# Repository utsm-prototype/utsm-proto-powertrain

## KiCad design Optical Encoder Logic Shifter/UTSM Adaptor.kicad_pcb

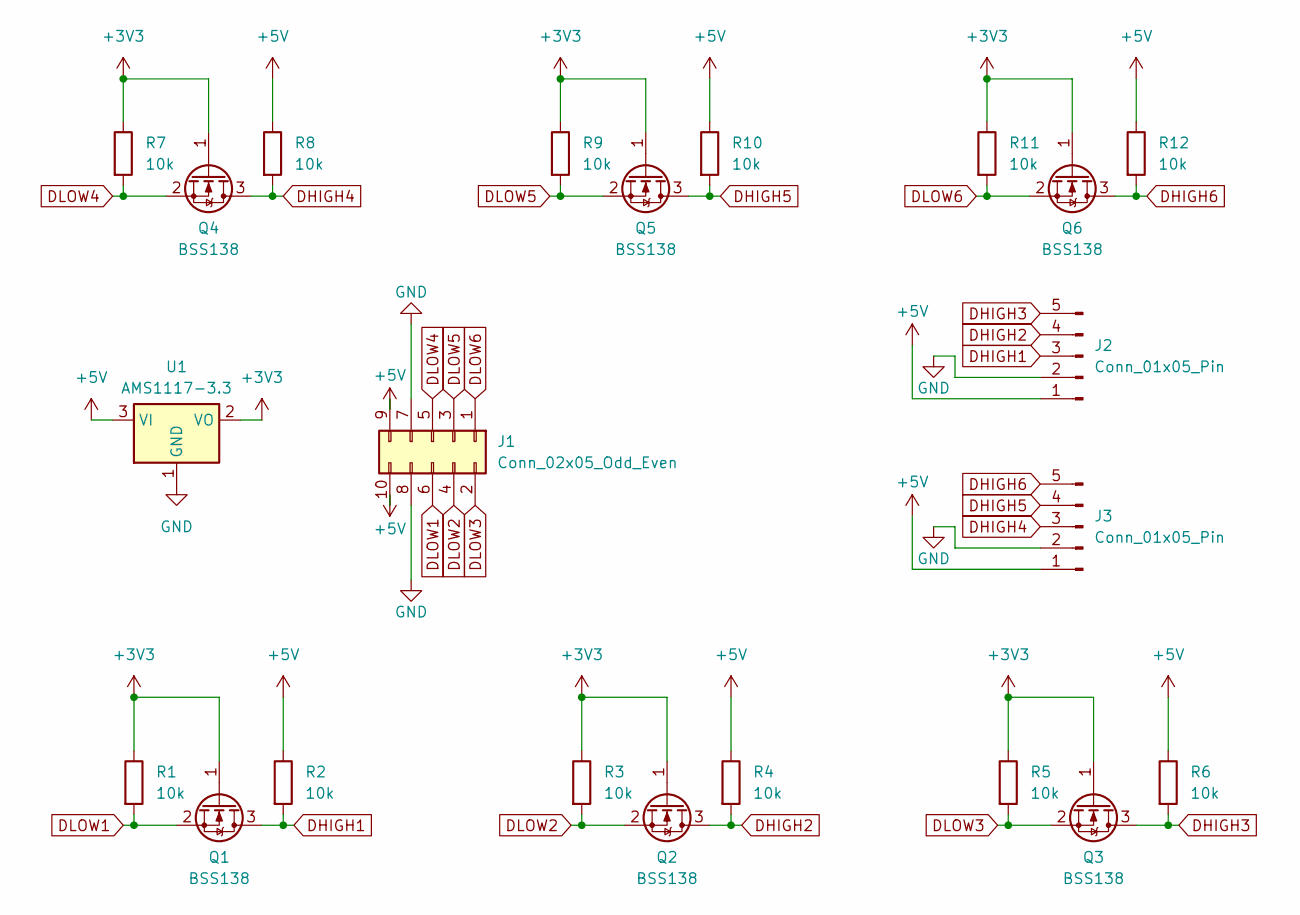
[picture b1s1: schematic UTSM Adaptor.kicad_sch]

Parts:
J1: Conn_02x05_Odd_Even; PinHeader_2x05_P2.54mm_Vertical
J2, J3: Conn_01x05_Pin; JST_PH_S5B-PH-K_1x05_P2.00mm_Horizontal
Q1, Q2, Q3, Q4, Q5, Q6: BSS138; SOT-23
R1, R2, R3, R4, R5, R6, R7, R8, R9, R10, R11, R12: 10k; R_0603_1608Metric_Pad0.98x0.95mm_HandSolder
U1: AMS1117-3.3; SOT-223-3_TabPin2

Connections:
+3V3: Q1.1 (G), Q2.1 (G), Q3.1 (G), Q4.1 (G), Q5.1 (G), Q6.1 (G), R1.1, R3.1, R5.1, R7.1, R9.1, R11.1, U1.2 (VO)
+5V: J1.9, J1.10, J2.1, J3.1, R2.1, R4.1, R6.1, R8.1, R10.1, R12.1, U1.3 (VI)
DHIGH1: J2.3, Q1.3 (D), R2.2
DHIGH2: J2.4, Q2.3 (D), R4.2
DHIGH3: J2.5, Q3.3 (D), R6.2
DHIGH4: J3.3, Q4.3 (D), R8.2
DHIGH5: J3.4, Q5.3 (D), R10.2
DHIGH6: J3.5, Q6.3 (D), R12.2
DLOW1: J1.6, Q1.2 (S), R1.2
DLOW2: J1.4, Q2.2 (S), R3.2
DLOW3: J1.2, Q3.2 (S), R5.2
DLOW4: J1.5, Q4.2 (S), R7.2
DLOW5: J1.3, Q5.2 (S), R9.2
DLOW6: J1.1, Q6.2 (S), R11.2
GND: J1.7, J1.8, J2.2, J3.2, U1.1 (GND)

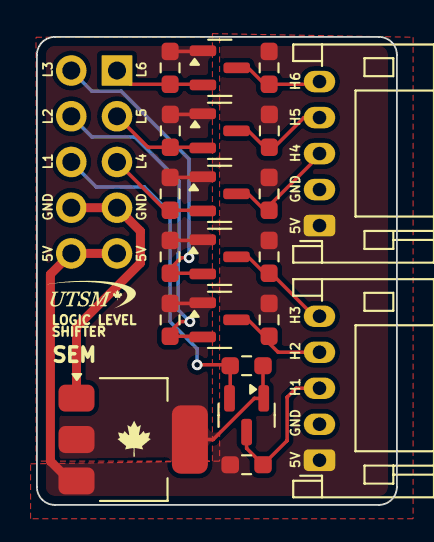
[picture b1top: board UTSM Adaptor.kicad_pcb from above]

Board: 2 copper layers, 20.0 x 26.0 mm, 22 parts (1 on the bottom side), 15 nets.

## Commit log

2025-02-14 Initial import
2025-02-14 Motor Controller 2
2025-02-14 implimented startup calibration function
2025-02-14 changed project name and cmake
2025-02-14 debug updates
2025-02-14 added encoder info
2025-02-14 added logic shifter
2025-03-22 upload code from andrew laptop
2025-03-22 added notebook file
